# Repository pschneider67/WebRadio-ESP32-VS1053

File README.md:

Here I show the hardware of a small Internet radio consisting of: 
- ESP32 
- VS1053b 
- 2.2" TFT display
- Amplifier module PAM8403

The boards were created with KiCad version 8.

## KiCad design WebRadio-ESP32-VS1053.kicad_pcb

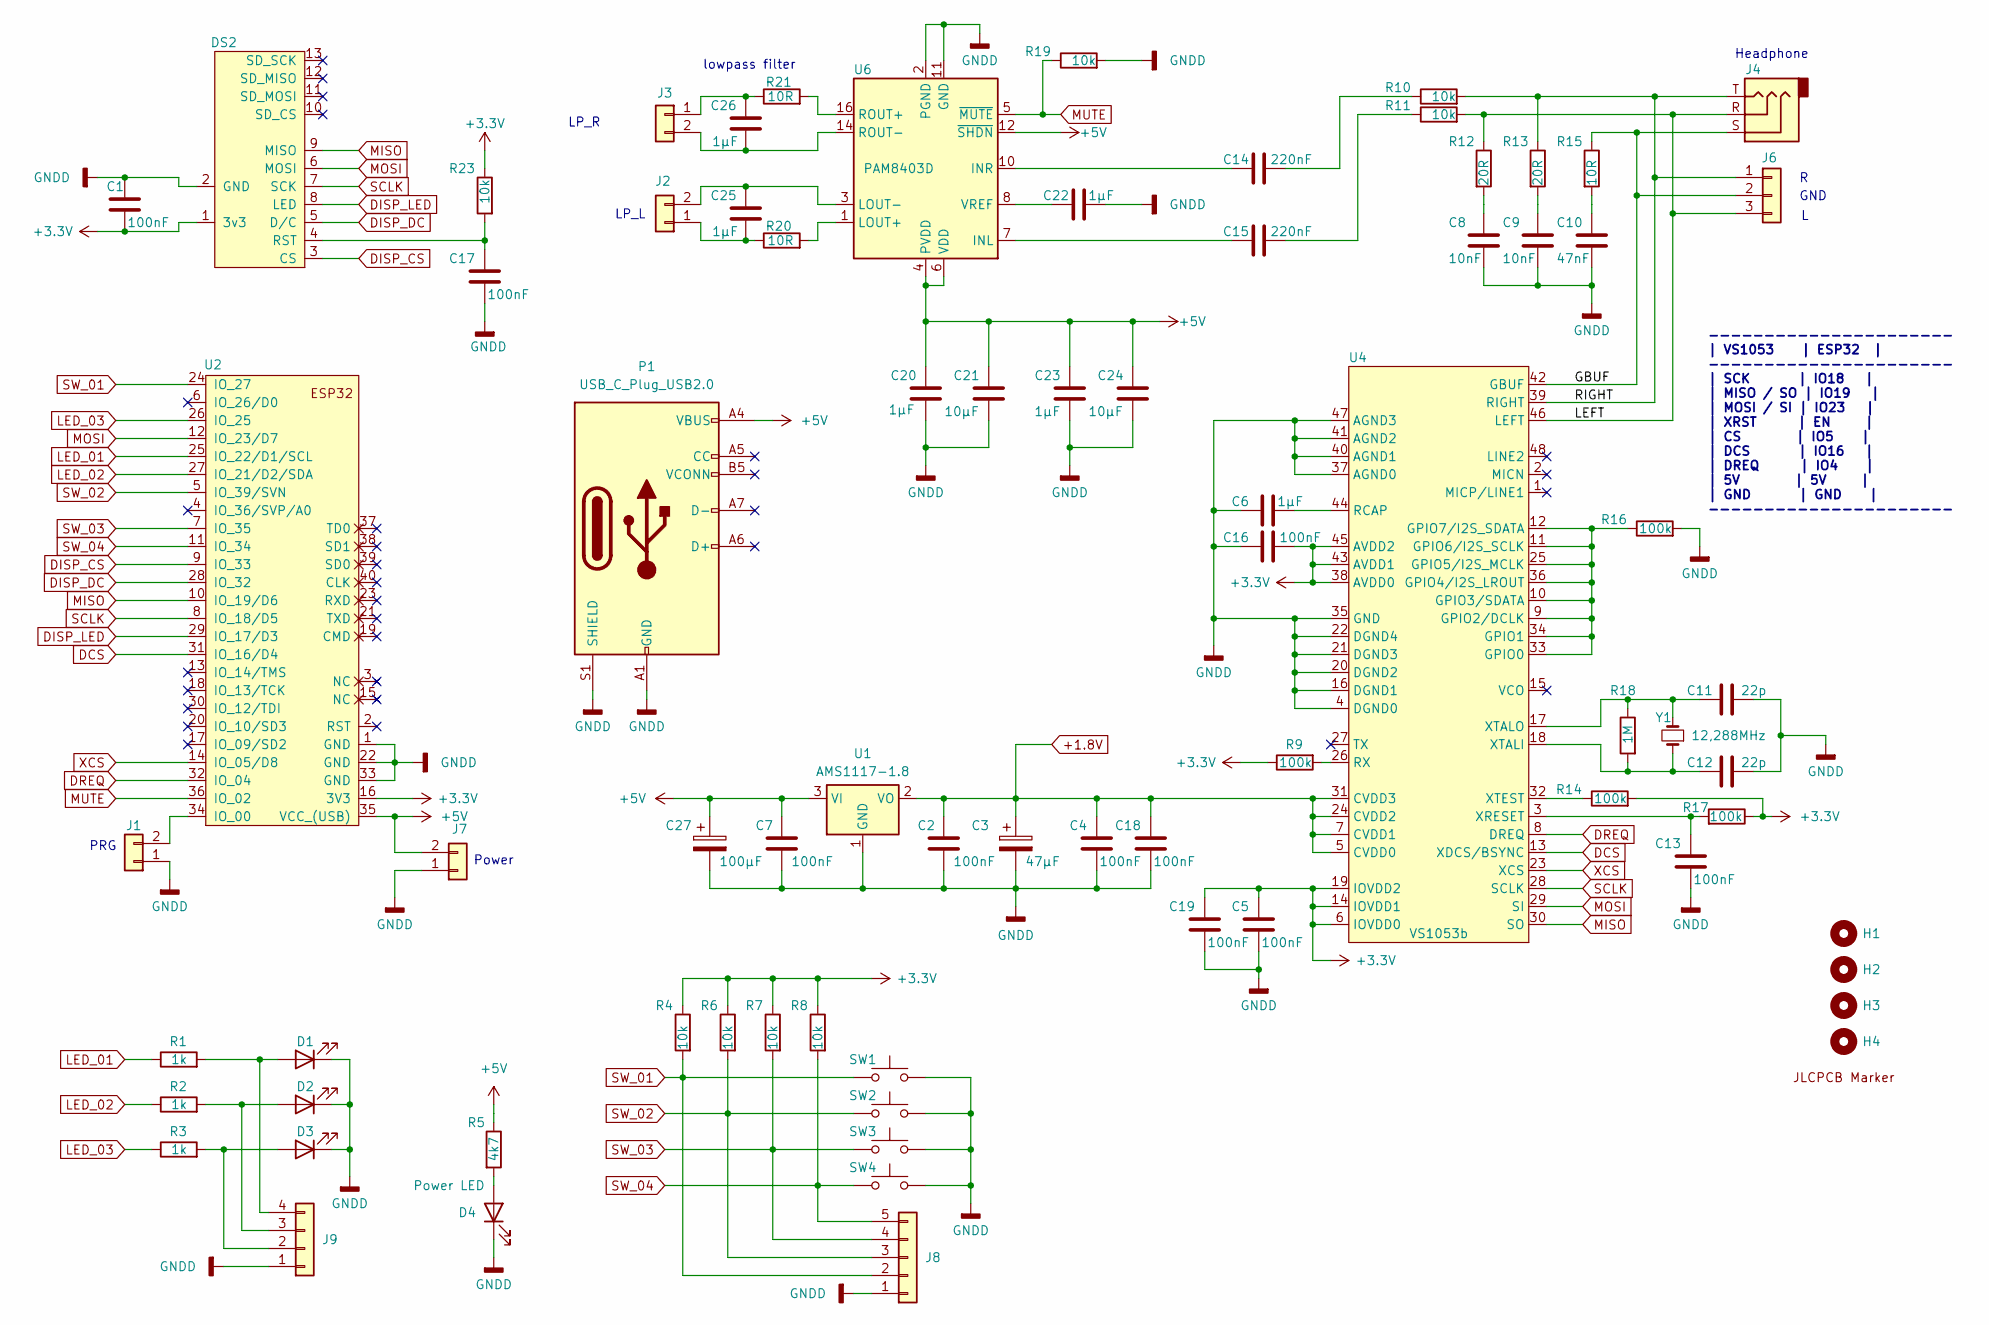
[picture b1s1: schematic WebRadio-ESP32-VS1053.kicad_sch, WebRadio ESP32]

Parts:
C1, C2, C4, C5, C7, C13, C16, C17, C18, C19: 100nF; C_1206_3216Metric_Pad1.33x1.80mm_HandSolder
C3: 47µF; CP_Elec_5x5.4
C6, C20, C22, C23, C25, C26: 1µF; C_1206_3216Metric_Pad1.33x1.80mm_HandSolder
C8, C9: 10nF; C_1206_3216Metric_Pad1.33x1.80mm_HandSolder
C10: 47nF; C_1206_3216Metric_Pad1.33x1.80mm_HandSolder
C11, C12: 22p; C_1206_3216Metric_Pad1.33x1.80mm_HandSolder
C14, C15: 220nF; C_1206_3216Metric_Pad1.33x1.80mm_HandSolder
C21, C24: 10µF; C_1206_3216Metric_Pad1.33x1.80mm_HandSolder
C27: 100µF; CP_Elec_5x5.4
D1, D2, D3: Power LED; LED_D3.0mm_SMD
D4: Power LED; LED_1206_3216Metric_Pad1.42x1.75mm_HandSolder
DS2: TFT2.2_SPI_4P_SD; TFT2.2_SPI_5P_SD
H1, H2, H3, H4: MountingHole; MountingHole_3.2mm_M3_ISO14580
J1: Conn_01x02; PinHeader_1x02_P2.54mm_Vertical
J2, J3, J7: JST PH 2mm; JST_PH_B2B-PH-K_1x02_P2.00mm_Vertical
J4: AudioJack3; Jack_3.5mm_SMT_Horizontal
J6: JST PH 2mm; JST_PH_B3B-PH-K_1x03_P2.00mm_Vertical
J8: Conn_01x05; JST_PH_B5B-PH-K_1x05_P2.00mm_Vertical
J9: Conn_01x04; JST_PH_B4B-PH-K_1x04_P2.00mm_Vertical
P1: USB_C_Plug_USB2.0; USB_C_Receptacle_GCT_USB4125-xx-x_6P_TopMnt_Horizontal
R1, R2, R3: 1k; R_1206_3216Metric_Pad1.30x1.75mm_HandSolder
R4, R6, R7, R8, R10, R11, R19, R23: 10k; R_1206_3216Metric_Pad1.30x1.75mm_HandSolder
R5: 4k7; R_1206_3216Metric_Pad1.30x1.75mm_HandSolder
R9, R14, R16, R17: 100k; R_1206_3216Metric_Pad1.30x1.75mm_HandSolder
R12, R13: 20R; R_1206_3216Metric_Pad1.30x1.75mm_HandSolder
R15, R20, R21: 10R; R_1206_3216Metric_Pad1.30x1.75mm_HandSolder
R18: 1M; R_1206_3216Metric_Pad1.30x1.75mm_HandSolder
SW1, SW2, SW3, SW4: SW_Push; SW_PUSH_6mm
U1: AMS1117-1.8; SOT-223
U2: mini_esp32; ESP32_mini
U4: VS1053b; LQFP-48_7x7mm_P0.5mm
U5: JLCPCB Marker; JLCPCB-Marker
U6: PAM8403D; SOP-16_3.9x9.9mm_P1.27mm
Y1: 12,288MHz; Crystal_HC49-U_Vertical

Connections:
+1.8V: C2.1, C3.1, C4.2, C18.2, U1.2 (VO), U4.5 (CVDD0), U4.7 (CVDD1), U4.24 (CVDD2), U4.31 (CVDD3)
+3.3V: C1.2, C5.2, C16.2, C19.2, DS2.1 (3v3), R4.1, R6.1, R7.1, R8.1, R9.1, R14.2, R17.1, R23.1, U2.16 (3V3), U4.6 (IOVDD0), U4.14 (IOVDD1), U4.19 (IOVDD2), U4.38 (AVDD0), U4.43 (AVDD1), U4.45 (AVDD2)
+5V: C7.1, C20.1, C21.1, C23.1, C24.1, C27.1, J7.2, P1.A4 (VBUS), P1.A9 (VBUS), P1.B4 (VBUS), P1.B9 (VBUS), R5.1, U1.3 (VI), U2.35 (VCC_(USB)), U6.4 (PVDD), U6.6 (VDD), U6.12 (~SHDN), U6.13 (PVDD)
/GBUF: J4.S, J6.2, R15.1, U4.42 (GBUF)
/LEFT: J4.R, J6.3, R11.2, R12.1, U4.46 (LEFT)
/RIGHT: J4.T, J6.1, R10.2, R13.1, U4.39 (RIGHT)
DCS: U2.31 (IO_16/D4), U4.13 (XDCS/BSYNC)
DISP_CS: DS2.3 (CS), U2.9 (IO_33)
DISP_DC: DS2.5 (D/C), U2.28 (IO_32)
DISP_LED: DS2.8 (LED), U2.29 (IO_17/D3)
DREQ: U2.32 (IO_04), U4.8 (DREQ)
GNDD: C1.1, C2.2, C3.2, C4.1, C5.1, C6.1, C7.2, C8.2, C9.2, C10.2, C11.1, C12.1, C13.1, C16.1, C17.2, C18.1, C19.1, C20.2, C21.2, C22.2, C23.2, C24.2, C27.2, D1.1 (K), D2.1 (K), D3.1 (K), D4.1 (K), DS2.2 (GND), J1.1, J7.1, J8.1, J9.1, P1.A1 (GND), P1.A12 (GND), P1.B1 (GND), P1.B12 (GND), P1.S1 (SHIELD), R16.2, R19.2, SW1.2, SW2.2, SW3.2, SW4.2, U1.1 (GND), U2.1 (GND), U2.22 (GND), U2.33 (GND), U4.4 (DGND0), U4.16 (DGND1), U4.20 (DGND2), U4.21 (DGND3), U4.22 (DGND4), U4.35 (GND), U4.37 (AGND0), U4.40 (AGND1), U4.41 (AGND2), U4.47 (AGND3), U6.2 (PGND), U6.11 (GND), U6.15 (PGND)
LED_01: R1.1, U2.25 (IO_22/D1/SCL)
LED_02: R2.1, U2.27 (IO_21/D2/SDA)
LED_03: R3.1, U2.26 (IO_25)
MISO: DS2.9 (MISO), U2.10 (IO_19/D6), U4.30 (SO)
MOSI: DS2.6 (MOSI), U2.12 (IO_23/D7), U4.29 (SI)
MUTE: R19.1, U2.36 (IO_02), U6.5 (~MUTE)
unnamed: C8.1, R12.2
unnamed: C9.1, R13.2
unnamed: C10.1, R15.2
unnamed: C14.2, R10.1
unnamed: C15.2, R11.1
unnamed: D1.2 (A), J9.4, R1.2
unnamed: D2.2 (A), J9.3, R2.2
unnamed: D3.2 (A), J9.2, R3.2
unnamed: D4.2 (A), R5.2
unnamed: C17.1, DS2.4 (RST), R23.2
unnamed: J1.2, U2.34 (IO_00)
unnamed: C25.2, J2.1, R20.1
unnamed: C25.1, J2.2, U6.3 (LOUT-)
unnamed: C26.1, J3.1, R21.1
unnamed: C26.2, J3.2, U6.14 (ROUT-)
unnamed: R16.1, U4.9 (GPIO2/DCLK), U4.10 (GPIO3/SDATA), U4.11 (GPIO6/I2S_SCLK), U4.12 (GPIO7/I2S_SDATA), U4.25 (GPIO5/I2S_MCLK), U4.33 (GPIO0), U4.34 (GPIO1), U4.36 (GPIO4/I2S_LROUT)
unnamed: C6.2, U4.44 (RCAP)
unnamed: R9.2, U4.26 (RX)
unnamed: C13.2, R17.2, U4.3 (XRESET)
unnamed: C12.2, R18.2, U4.18 (XTALI), Y1.1
unnamed: C11.2, R18.1, U4.17 (XTALO), Y1.2
unnamed: R14.1, U4.32 (XTEST)
unnamed: C15.1, U6.7 (INL)
unnamed: C14.1, U6.10 (INR)
unnamed: R20.2, U6.1 (LOUT+)
unnamed: R21.2, U6.16 (ROUT+)
unnamed: C22.1, U6.8 (VREF)
SCLK: DS2.7 (SCK), U2.8 (IO_18/D5), U4.28 (SCLK)
SW_01: J8.2, R4.2, SW1.1, U2.24 (IO_27)
SW_02: J8.3, R6.2, SW2.1, U2.5 (IO_39/SVN)
SW_03: J8.4, R7.2, SW3.1, U2.7 (IO_35)
SW_04: J8.5, R8.2, SW4.1, U2.11 (IO_34)
XCS: U2.14 (IO_05/D8), U4.23 (XCS)

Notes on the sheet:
PRG
LP_L
LP_R
Power
GND
---------------------- | VS1053 | ESP32 | ---------------------- | SCK | IO18 | | MISO / SO | IO19 | | MOSI / SI | IO23 | | XRST | EN | | CS | IO5 | | DCS | IO16 | | DREQ | IO4 | | 5V | 5V | | GND | GND | ----------------------
Headphone
lowpass filter

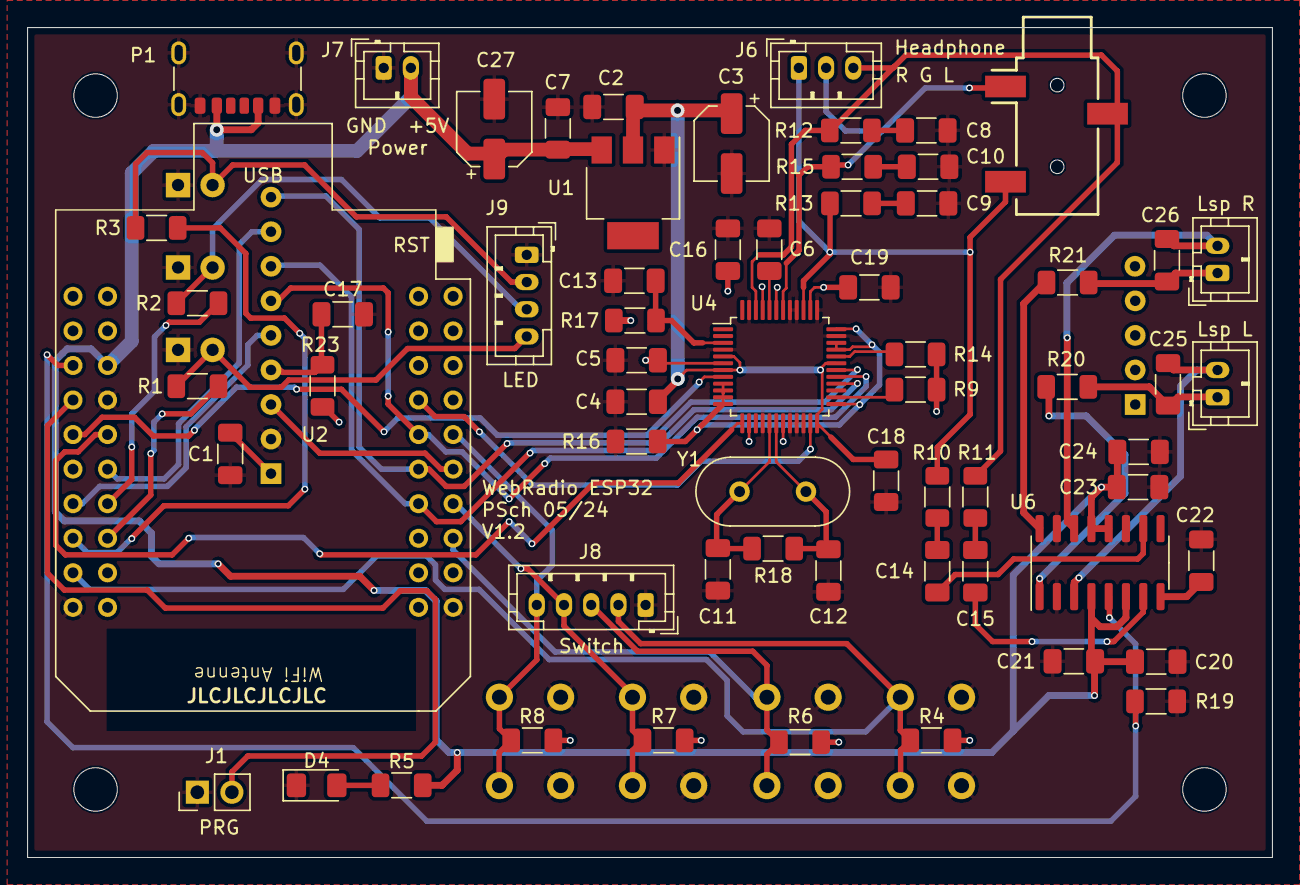
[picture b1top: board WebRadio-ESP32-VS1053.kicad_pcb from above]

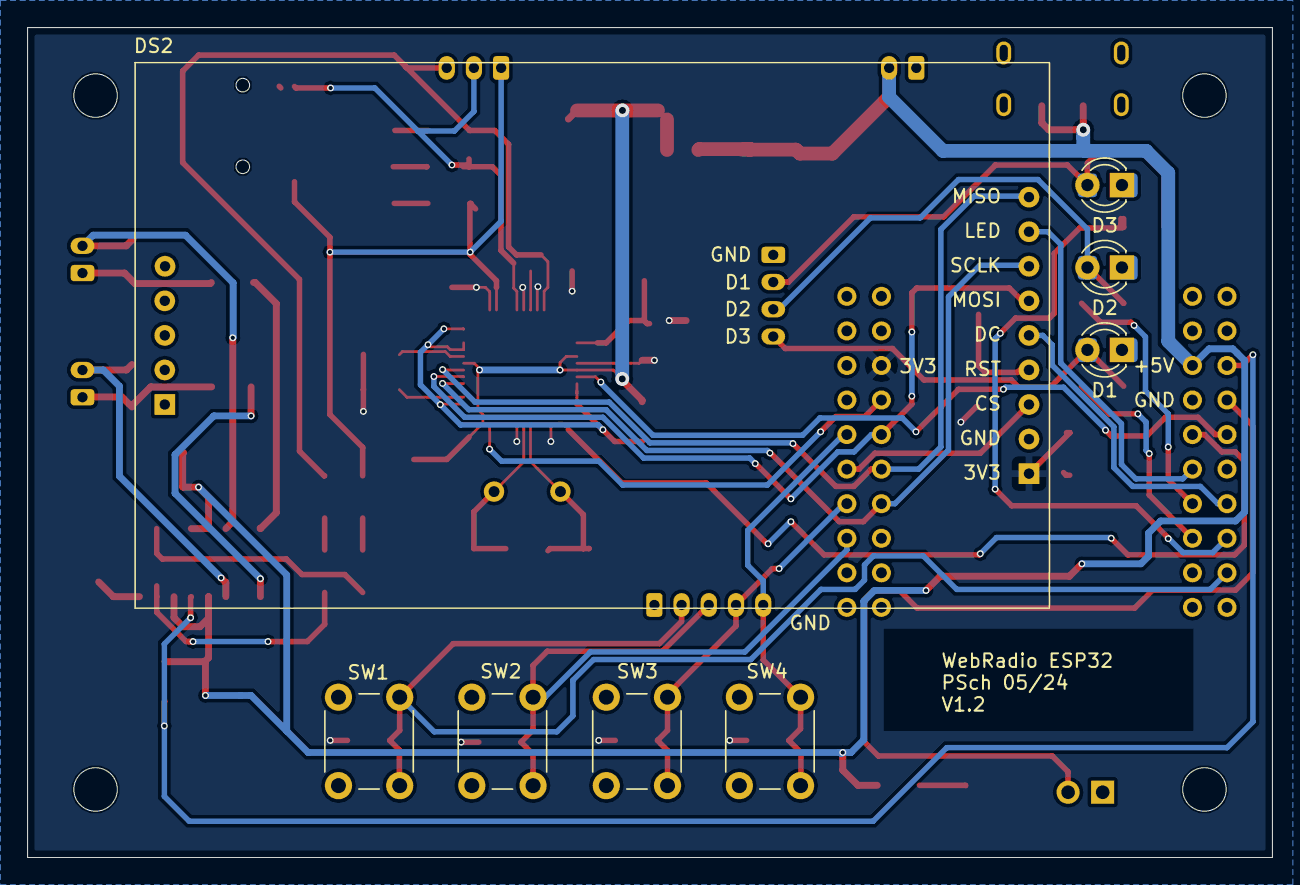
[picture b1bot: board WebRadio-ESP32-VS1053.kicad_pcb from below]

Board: 2 copper layers, 91.5 x 61.0 mm, 77 parts (8 on the bottom side), 51 nets.

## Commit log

2024-05-20 first commit
    KiCad data of a small internet radio with ESP32 and VS1053 decoder chip.
2024-05-24 include power over usb-c and jst connector
2024-05-24 add local library
2024-05-24 change some comments
2024-05-25 add new footrint for 3mm LED to us also SMD LED's
2024-05-26 add audio output connector
2024-05-26 add labeling
2024-05-26 change date of drawing
2024-05-27 add pin header for leds and swiches
2024-05-30 include JST PH connectors
2024-06-03 change some silkscreen data
